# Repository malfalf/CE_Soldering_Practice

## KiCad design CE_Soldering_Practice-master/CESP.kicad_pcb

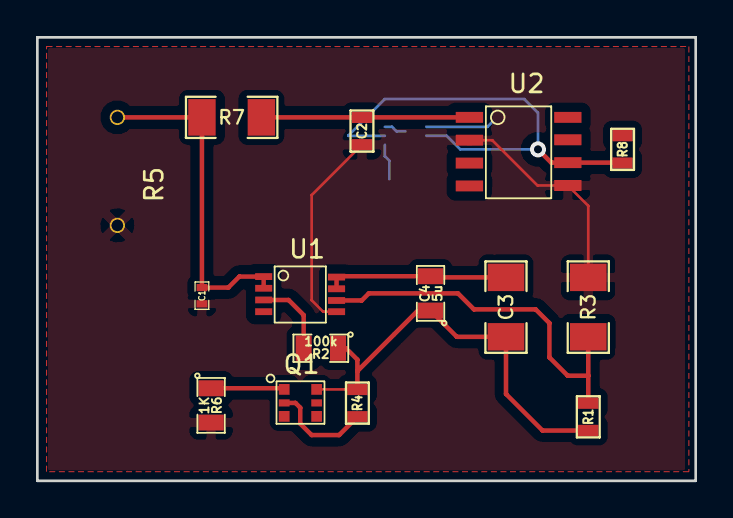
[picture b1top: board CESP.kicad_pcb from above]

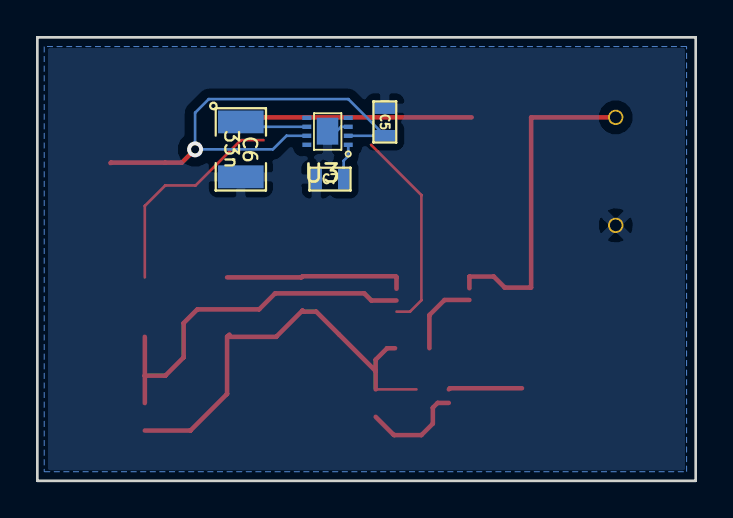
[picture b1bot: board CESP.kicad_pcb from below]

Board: 2 copper layers, 36.6 x 24.6 mm, 19 parts (4 on the bottom side), 12 nets.

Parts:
C1: 1u; SM0402
C2: 10u; SM0603
C3: 5u; SM1206
C4: 5u; SM0805
C5, C7: 2.2u; SM0603
C6: 33n; SM1210
Q1: BSS84AKS_P_MOSFET; BSS84AKS
R1: 10K; SM0603
R2: 100k; SM0805
R3: 1K; SM1206
R4, R8: 1K; SM0603
R5: VDRH05B011xyE; VDRH05B011xyE-TH
R6: 1K; SM0805
R7: 10k; SM1206
U1: RT9186AGF_-_LDO; RT9186AGF
U2: MOC205M
U3: LP3982

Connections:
GND: C1.2, C2.2, C5.2, C6.2, C7.2, R3.2, R5.2, R6.2, U1.5, U2.2, U2.5, U3.3, U3.9
LDO_1_Output: C3.1, C4.1, Q1.6, R1.1, R2.1, R4.1
LDO_2_Output: C7.1, U3.1
unnamed: Q1.2, R4.2
unnamed: Q1.1, R6.1
unnamed: C6.1, U3.6
unnamed: R1.2, R3.1, U1.6
unnamed: C2.1, R7.2, U2.1
unnamed: C3.2, C4.2, U1.7, U1.8
unnamed: R2.2, U1.3
OptoOutput: C5.1, R8.2, U2.6, U3.2, U3.7
V_input: C1.1, R5.1, R7.1, U1.1, U1.2

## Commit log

2014-01-26 Nuestro primer commit
2014-01-26 My practice
2014-01-26 My CE soldering practice
